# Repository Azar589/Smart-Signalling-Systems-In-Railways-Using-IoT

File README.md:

Here is a comprehensive and professionally structured README file for your project, incorporating all the provided details and code logic.

***

# Smart Signalling Systems in Railways

**Author**: Mohamed Azarudeen F.

## 📖 Abstract
The Smart Signalling System for Railways addresses critical visibility challenges faced by locomotive pilots, especially during adverse weather conditions such as fog and rain. The project introduces an advanced signalling solution using RF transceiver technology to ensure reliable, real-time communication between trackside signals and locomotives. 

By integrating RF transceivers with microcontrollers (ESP32 and Arduino Nano), trackside signal data is transmitted directly to a display monitor inside the train, entirely eliminating the dependency on visual cues. This system significantly enhances safety, reduces travel delays, and minimizes human error. Built with a focus on scalability, cost-effectiveness, and future IoT integration, it aligns with multiple UN Sustainable Development Goals by emphasizing innovation, safety, and infrastructure development.

## ✨ Key Features
* **Real-Time RF Communication**: Sends trackside status updates (RED, YELLOW, GREEN) to the locomotive instantaneously upon status change.
* **Robust Security Protocols**: Implements an XOR cipher with a predefined secret key (`0x5A`) for encrypting payload data.
* **Anti-Replay Attack Protection**: Utilizes incrementing sequence numbers to validate incoming packets and reject malicious replay attempts.
* **Device Authentication**: Enforces strict verification using a unique Device ID (`TX1`) to ensure the receiver only processes data from authorized trackside transmitters.
* **IoT Cloud Integration**: Securely uploads validated signal data to the ThingSpeak cloud platform over WiFi, utilizing a 16-second rate limit to comply with API constraints.
* **Local Web Dashboard**: Includes a custom Node.js server to host a real-time web monitoring dashboard (`Signal_Monitor_Web.html`) over port 8080.

## 🛠️ Hardware Requirements
* **Microcontrollers**: ESP32 (for the Receiver/Locomotive unit with WiFi capabilities) and Arduino Nano (for the Transmitter/Trackside unit).
* **Communication**: RF Transceiver modules compatible with the `RH_ASK` library.
* **Sensors/Indicators**: Trackside signal switches/sensors and corresponding LEDs for local status visualization.

## 💻 System Architecture

### 1. Transmitter Unit (`Tx_Unit.cpp`)
Located at the trackside, this unit reads digital inputs representing the current signal status (RED, YELLOW, GREEN). It monitors for state changes to reduce unnecessary RF traffic. When a change is detected, it formats a comma-separated payload containing the Device ID, an incrementing Sequence Number, and the Signal Status. The payload is then encrypted via XOR cipher and broadcasted over RF.

### 2. Receiver Unit (`Rx_Unit.cpp`)
Located inside the locomotive, this unit continuously listens for RF transmissions. Upon receiving a packet, it decrypts the string and extracts the comma-separated values. The unit verifies the `DEVICE_ID` and ensures the sequence number is strictly greater than the previously recorded sequence to prevent replay attacks. If valid, the new status is printed to the serial monitor and uploaded to a ThingSpeak channel via an HTTP GET request.

### 3. Web Dashboard Server (`server.js`)
A lightweight Node.js web server that serves the UI files (`.html`, `.css`, `.js`). Once started, it listens on port 8080 and provides a centralized interface for monitoring the IoT data sent by the trains. 

## 🚀 Installation and Setup

### Embedded Code Setup (Arduino IDE)
1.  **Dependencies**: Install the required C++ libraries via the Arduino Library Manager:
    * `RH_ASK` (RadioHead library for RF communication)
    * `WiFi` and `HTTPClient` (For ESP32 IoT connectivity)
2.  **Configuration**: 
    * In `Rx_Unit.cpp`, update the WiFi credentials (`WiFi.begin("SSID", "PASSWORD");`) to match your network.
    * Ensure your ThingSpeak API key is correctly set in the `thingSpeakWrite()` function URL.
3.  **Flashing**: Upload `Tx_Unit.cpp` to the Arduino Nano and `Rx_Unit.cpp` to the ESP32 using a baud rate of `115200`.

### Web Server Setup
1.  Navigate to the `Website` directory containing `server.js`.
2.  Ensure Node.js is installed on your machine.
3.  Run the server from the terminal:
    ```bash
    node server.js
    ```
4.  Open a browser and navigate to `http://localhost:8080` to access the dashboard.

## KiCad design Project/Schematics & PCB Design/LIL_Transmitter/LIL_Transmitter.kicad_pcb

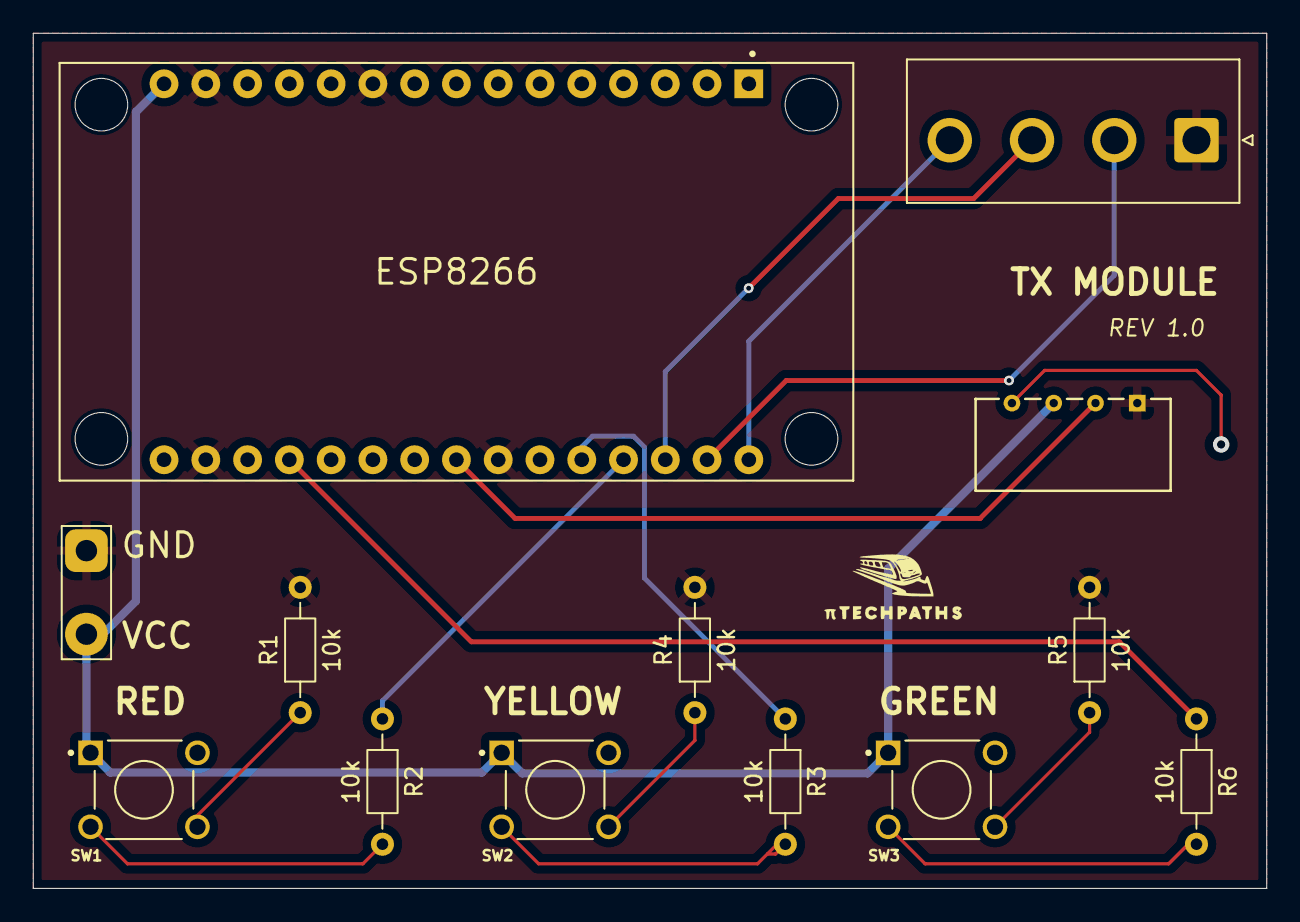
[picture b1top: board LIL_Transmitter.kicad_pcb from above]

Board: 2 copper layers, 75.0 x 52.0 mm, 13 parts (0 on the bottom side), 15 nets.

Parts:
J1: OUTPUT; JST_NV_B04P-NV_1x04_P5.00mm_Vertical
R1, R2, R3, R4, R5, R6: 10k; R_Axial_DIN0204_L3.6mm_D1.6mm_P7.62mm_Horizontal
SW1, SW2, SW3: 1825910-6; SW_1825910-6-4
TP1: INPUT; TestPoint_2Pads_Pitch5.08mm_Drill1.3mm
U1: QAM-TX2-433; QAM-TX2-433_RFS
U2: ESP8266; MODULE_ZC563900

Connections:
/DAT: U1.2 (IN), U2.23 (D5)
/G: R6.1, U2.19 (RX)
/G1: J1.4, U2.30 (D0)
/R: R2.1, U2.27 (D3)
/R1: J1.2, U2.29 (D1)
/Y: R3.1, U2.26 (D4)
/Y1: J1.3, U2.28 (D2)
GND: J1.1, R1.2, R4.2, R5.2, TP1.1, U1.1 (GND), U2.10 (GND), U2.14 (GND), U2.17 (GND), U2.24 (GND)
unnamed: R1.1, SW1.4
unnamed: R2.2, SW1.3
unnamed: R3.2, SW2.3
unnamed: R4.1, SW2.4
unnamed: R5.1, SW3.4
unnamed: R6.2, SW3.3
VCC: SW1.1, SW2.1, SW3.1, TP1.2, U1.3 (VCC), U2.15 (VIN)

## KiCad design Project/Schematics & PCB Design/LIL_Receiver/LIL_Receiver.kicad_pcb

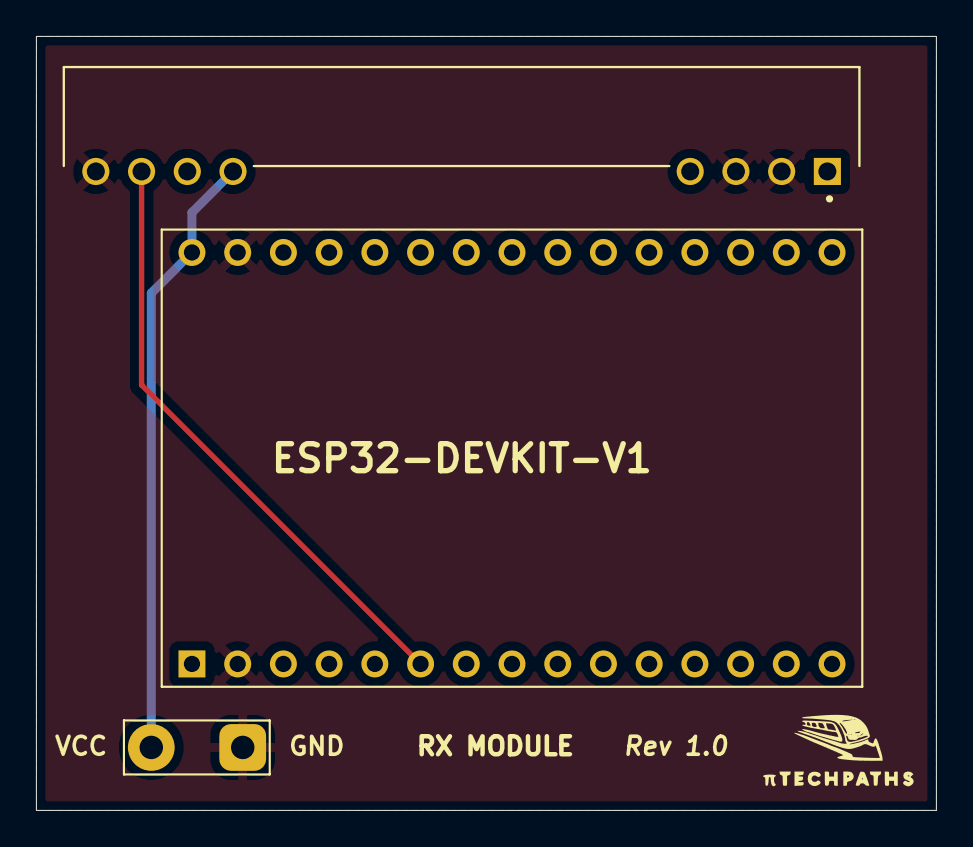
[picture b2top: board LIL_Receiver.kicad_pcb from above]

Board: 2 copper layers, 50.0 x 43.0 mm, 3 parts (0 on the bottom side), 3 nets.

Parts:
TP1: INPUT; TestPoint_2Pads_Pitch5.08mm_Drill1.3mm
U1: ESP32-DEVKIT-V1; ESP32-C3-DevKitM-1
U2: QFM-RX1-433; MODULE_QFM-RX1-433

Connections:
/DAT: U1.6 (RX2), U2.7 (DATA_OUTPUT)
GND: TP1.1, U1.2 (GND), U1.29 (GND), U2.2 (GROUND), U2.3 (GROUND), U2.8 (GROUND)
VCC: TP1.2, U1.30 (VIN), U2.4 (SUPPLY_VOLTAGE), U2.5 (SUPPLY_VOLTAGE)

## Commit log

2026-03-06 Create Signal_Monitor_Web
    A Simple Website to Monitor IoT Data
2026-03-06 Signal_Monitor_Web
2026-03-06 Update Signal_Monitor_Web
2026-03-06 Rename Signal_Monitor_Web to Signal_Monitor_Web.html
2026-03-06 Updated Dahboard and Settings
2026-03-06 Added project overview for Smart Signalling System
    The README introduces the Smart Signalling System for Railways, detailing its purpose, technology, and benefits.
2026-03-06 Add project abstract for Smart Signalling System
    Added an abstract for the Smart Signalling System project, detailing its purpose and technology.
2026-03-06 Enhance project abstract in README
    Expanded the abstract to detail the project's objectives and technology.
2026-03-08 Signal History Bar Graph Updated
2026-03-11 Moved to New Folder
2026-03-11 Moved out from folder
2026-03-11 Project codes added to github
2026-03-11 Code Updated for stablity
2026-03-11 Code Updated to Improv Security
2026-03-15 Demo Account Added
2026-03-29 Files Organized and Schematics & PCB Designs added
2026-03-30 Tx Code Optimized for board safety concerns
2026-03-31 Schematics & PCB Designs Updated
2026-04-13 Rx Unit bug cleared and Rx unit version 2 uploded
2026-04-14 Website updated
2026-05-17 Rx Unit V2 Updated
